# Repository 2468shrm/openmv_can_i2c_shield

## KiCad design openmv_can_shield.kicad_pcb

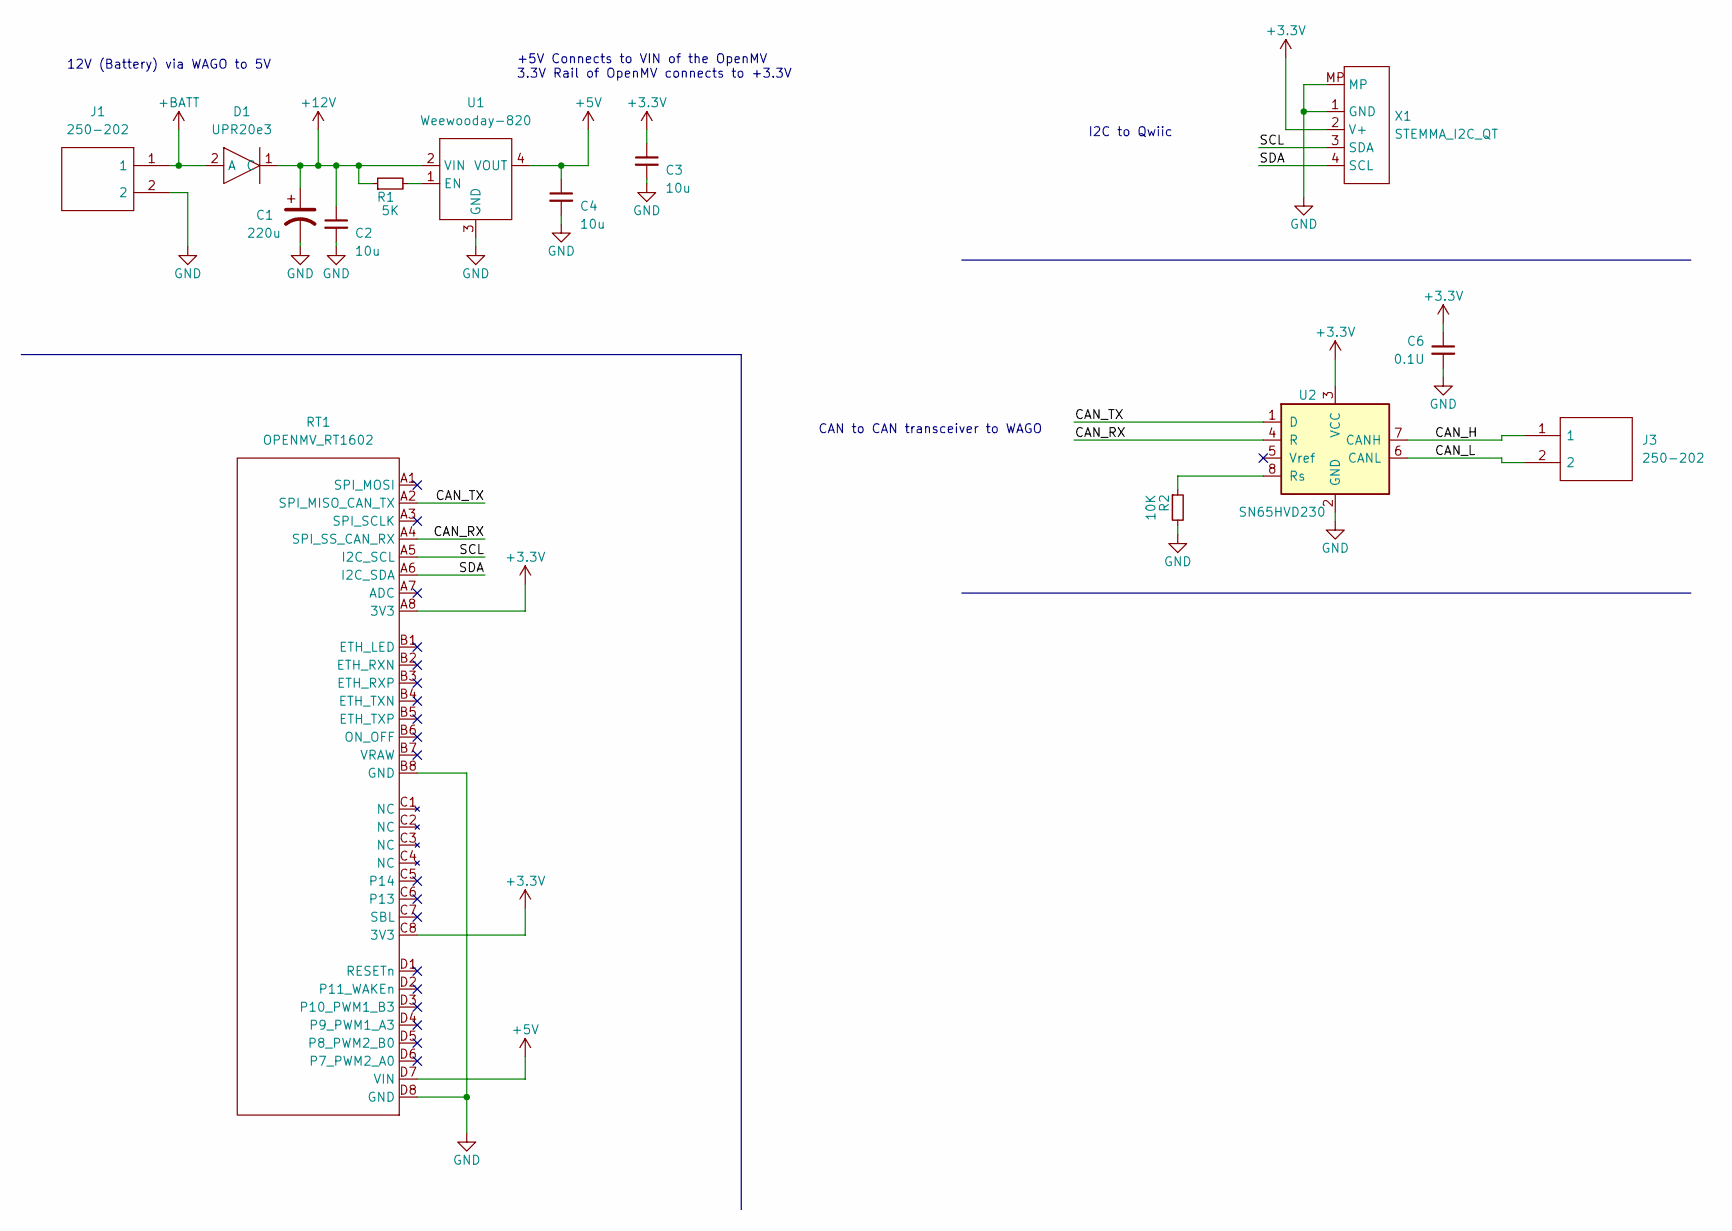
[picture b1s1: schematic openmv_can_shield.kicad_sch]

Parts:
C1: 220u; CP_Elec_6.3x7.7; LCSC C340767
C2, C3, C4: 10u; C_1206_3216Metric; LCSC C14860
C6: 0.1U; C_1206_3216Metric
D1: UPR20e3; DO-216
J1, J3: 250-202; 250202; Manufacturer_Part_Number 250-202
R1: 5K; R_1206_3216Metric
R2: 10K; R_1206_3216Metric
RT1: OPENMV_RT1602; RT1062
U1: Weewooday-820
U2: SN65HVD230; SOIC-8_3.9x4.9mm_P1.27mm
X1: STEMMA_I2C_QT; JST_SH_BM04B-SRSS-TB_1x04-1MP_P1.00mm_Vertical; LCSC C545725

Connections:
+3.3V: C3.1, C6.1, RT1.A8 (3V3), RT1.C8 (3V3), U2.3 (VCC), X1.2 (V+)
+5V: C4.1, RT1.D7 (VIN), U1.4 (VOUT)
+12V: C1.1, C2.1, D1.1 (C), R1.1, U1.2 (VIN)
+BATT: D1.2 (A), J1.1
/CAN_H: J3.1, U2.7 (CANH)
/CAN_L: J3.2, U2.6 (CANL)
/CAN_RX: RT1.A4 (SPI_SS_CAN_RX), U2.4 (R)
/CAN_TX: RT1.A2 (SPI_MISO_CAN_TX), U2.1 (D)
/SCL: RT1.A5 (I2C_SCL), X1.3 (SDA)
/SDA: RT1.A6 (I2C_SDA), X1.4 (SCL)
GND: C1.2, C2.2, C3.2, C4.2, C6.2, J1.2, R2.2, RT1.B8 (GND), RT1.D8 (GND), U1.3 (GND), U2.2 (GND), X1.1 (GND), X1.MP
unnamed: R1.2, U1.1 (EN)
unnamed: R2.1, U2.8 (Rs)

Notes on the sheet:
CAN to CAN transceiver to WAGO
+5V Connects to VIN of the OpenMV 3.3V Rail of OpenMV connects to +3.3V
I2C to Qwiic
12V (Battery) via WAGO to 5V

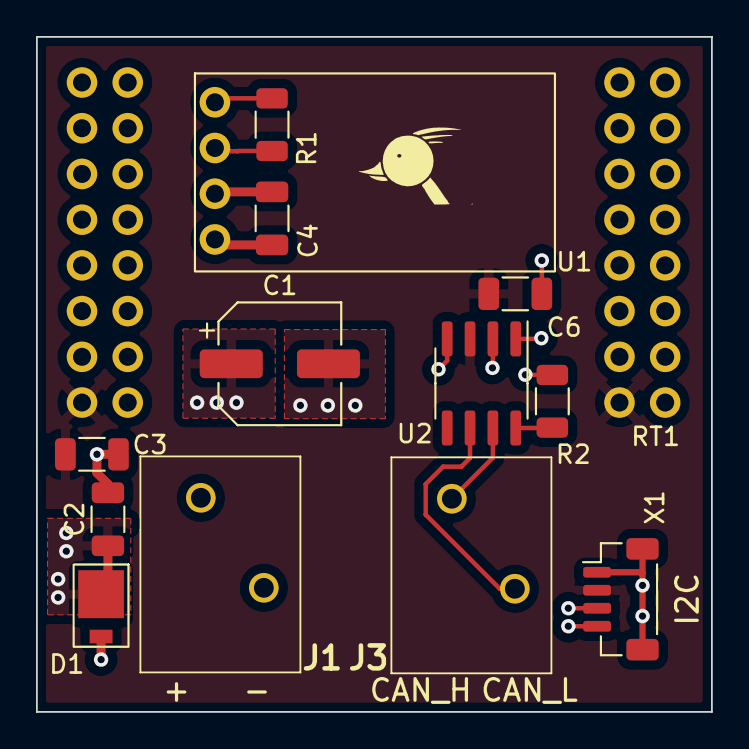
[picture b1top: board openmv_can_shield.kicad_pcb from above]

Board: 4 copper layers, 37.5 x 37.5 mm, 14 parts (0 on the bottom side), 13 nets.

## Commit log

2024-02-24 PCB files

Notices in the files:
openmv_can_shield.kicad_pcb:
(c) 2024, SHRM
All Rights Reserved
